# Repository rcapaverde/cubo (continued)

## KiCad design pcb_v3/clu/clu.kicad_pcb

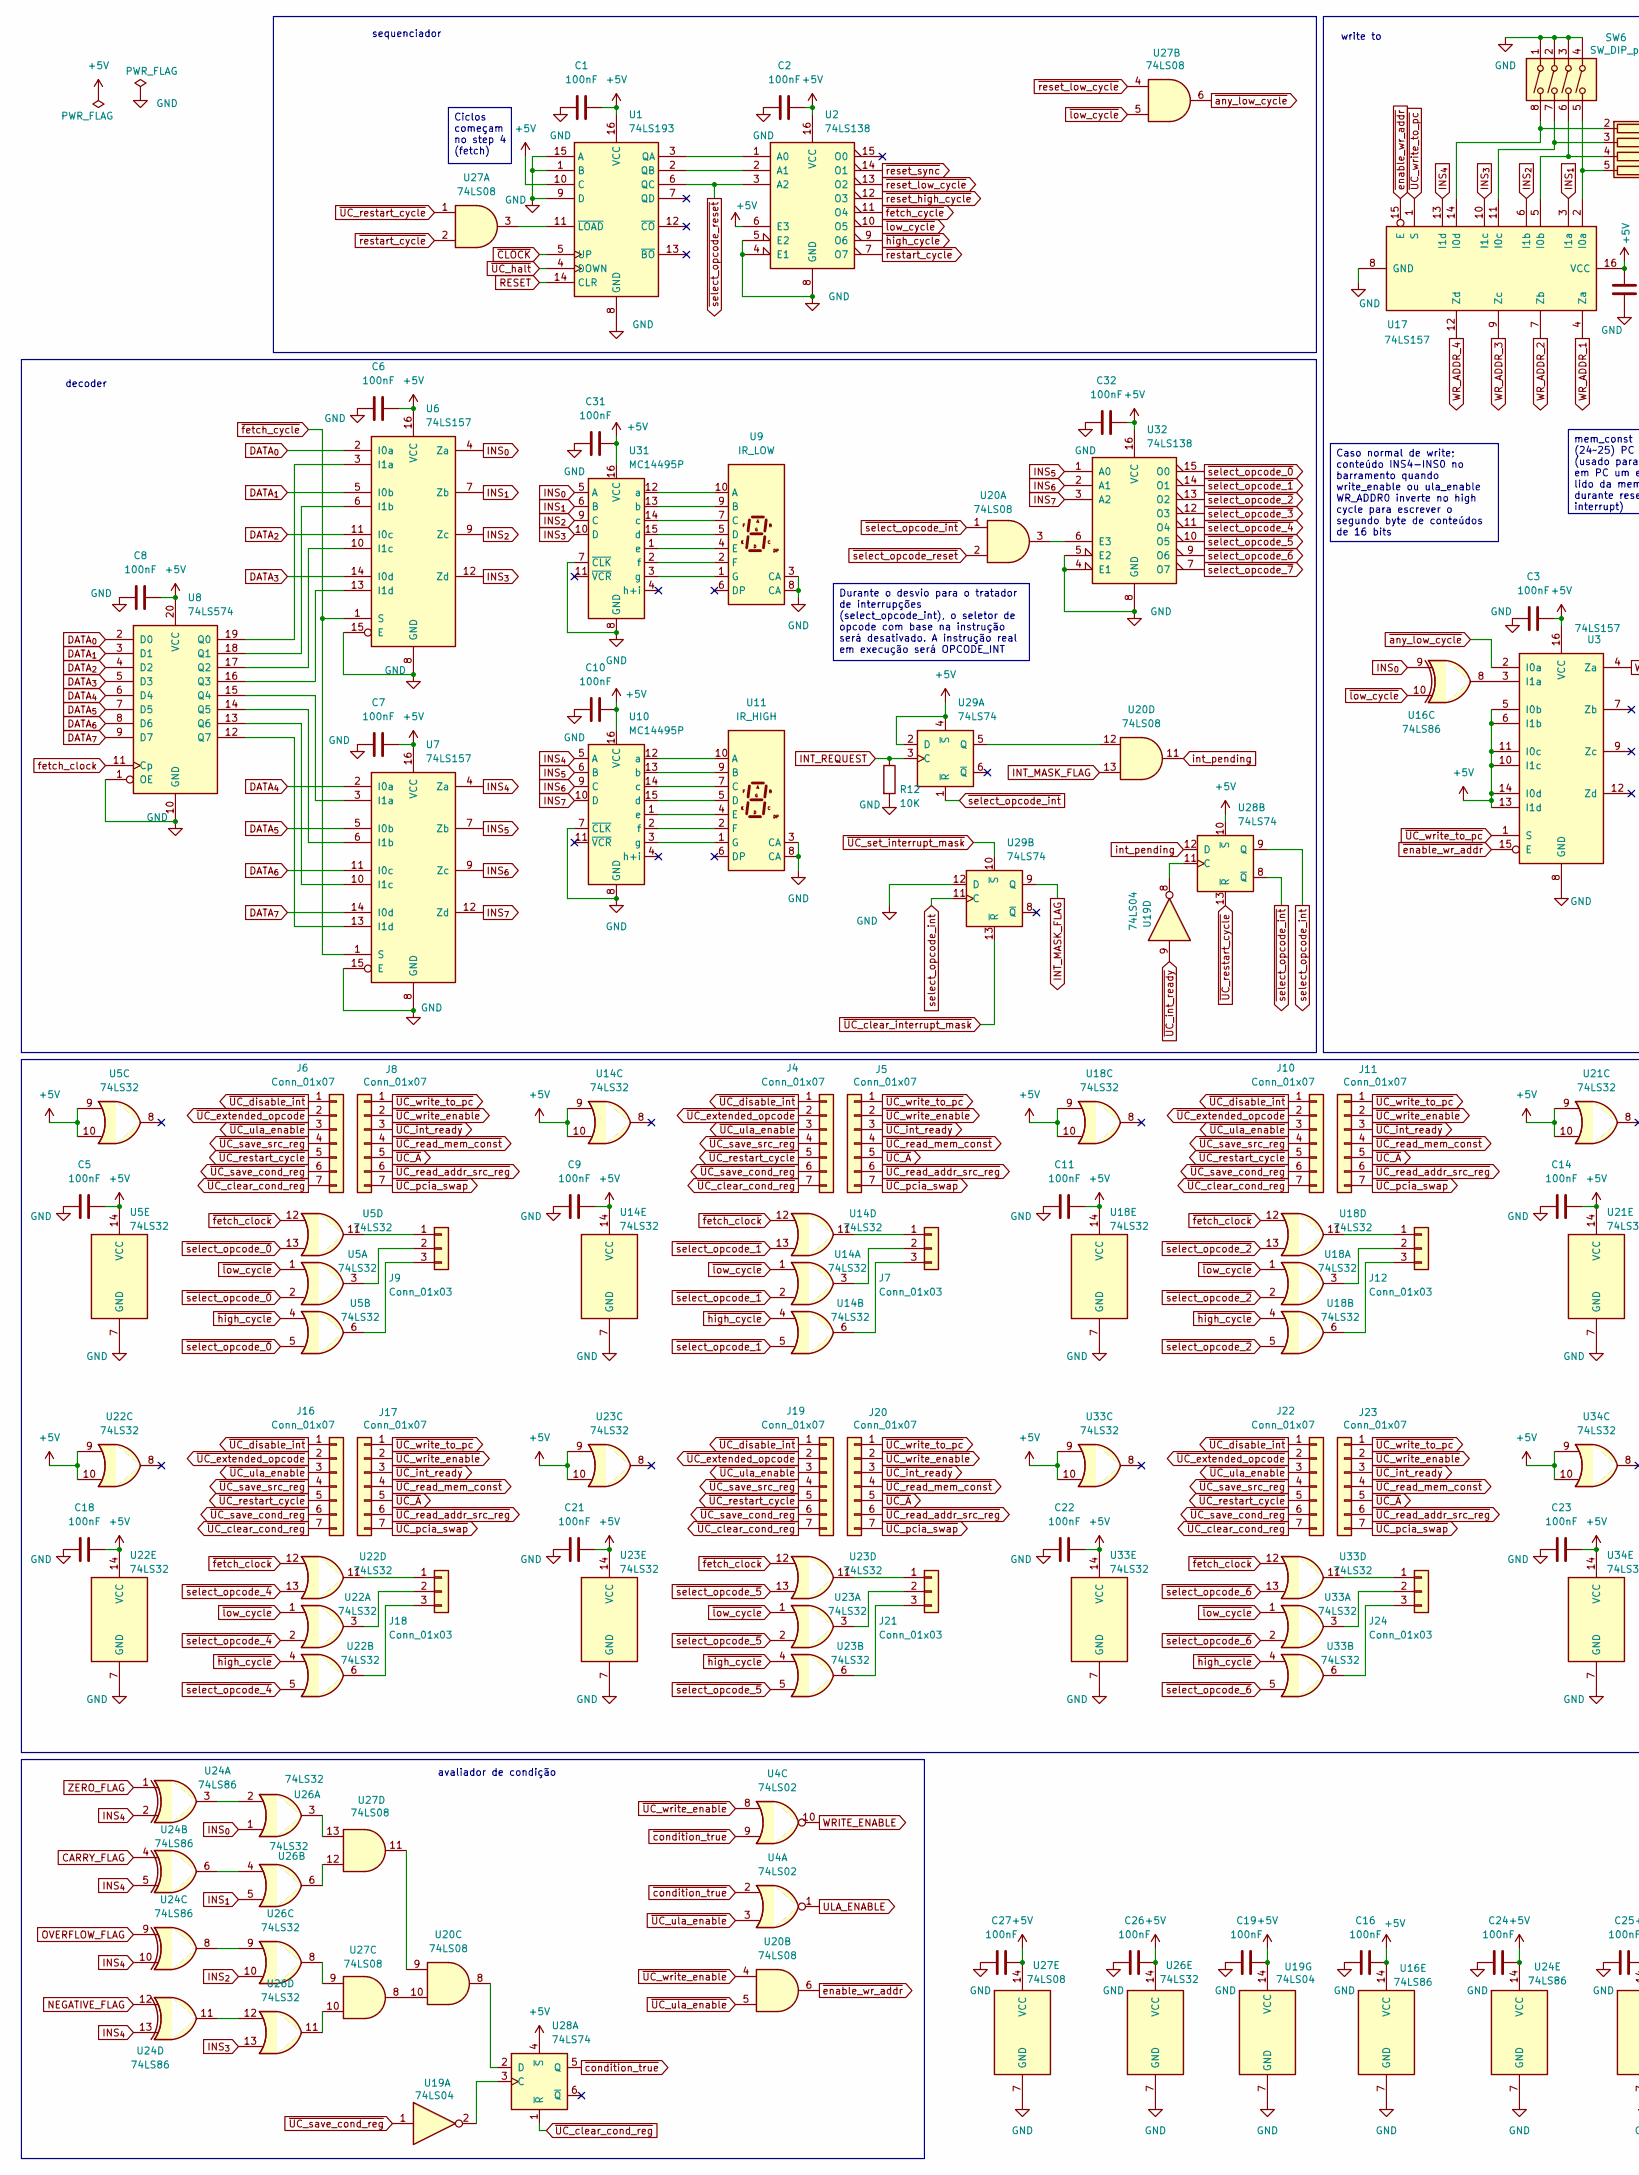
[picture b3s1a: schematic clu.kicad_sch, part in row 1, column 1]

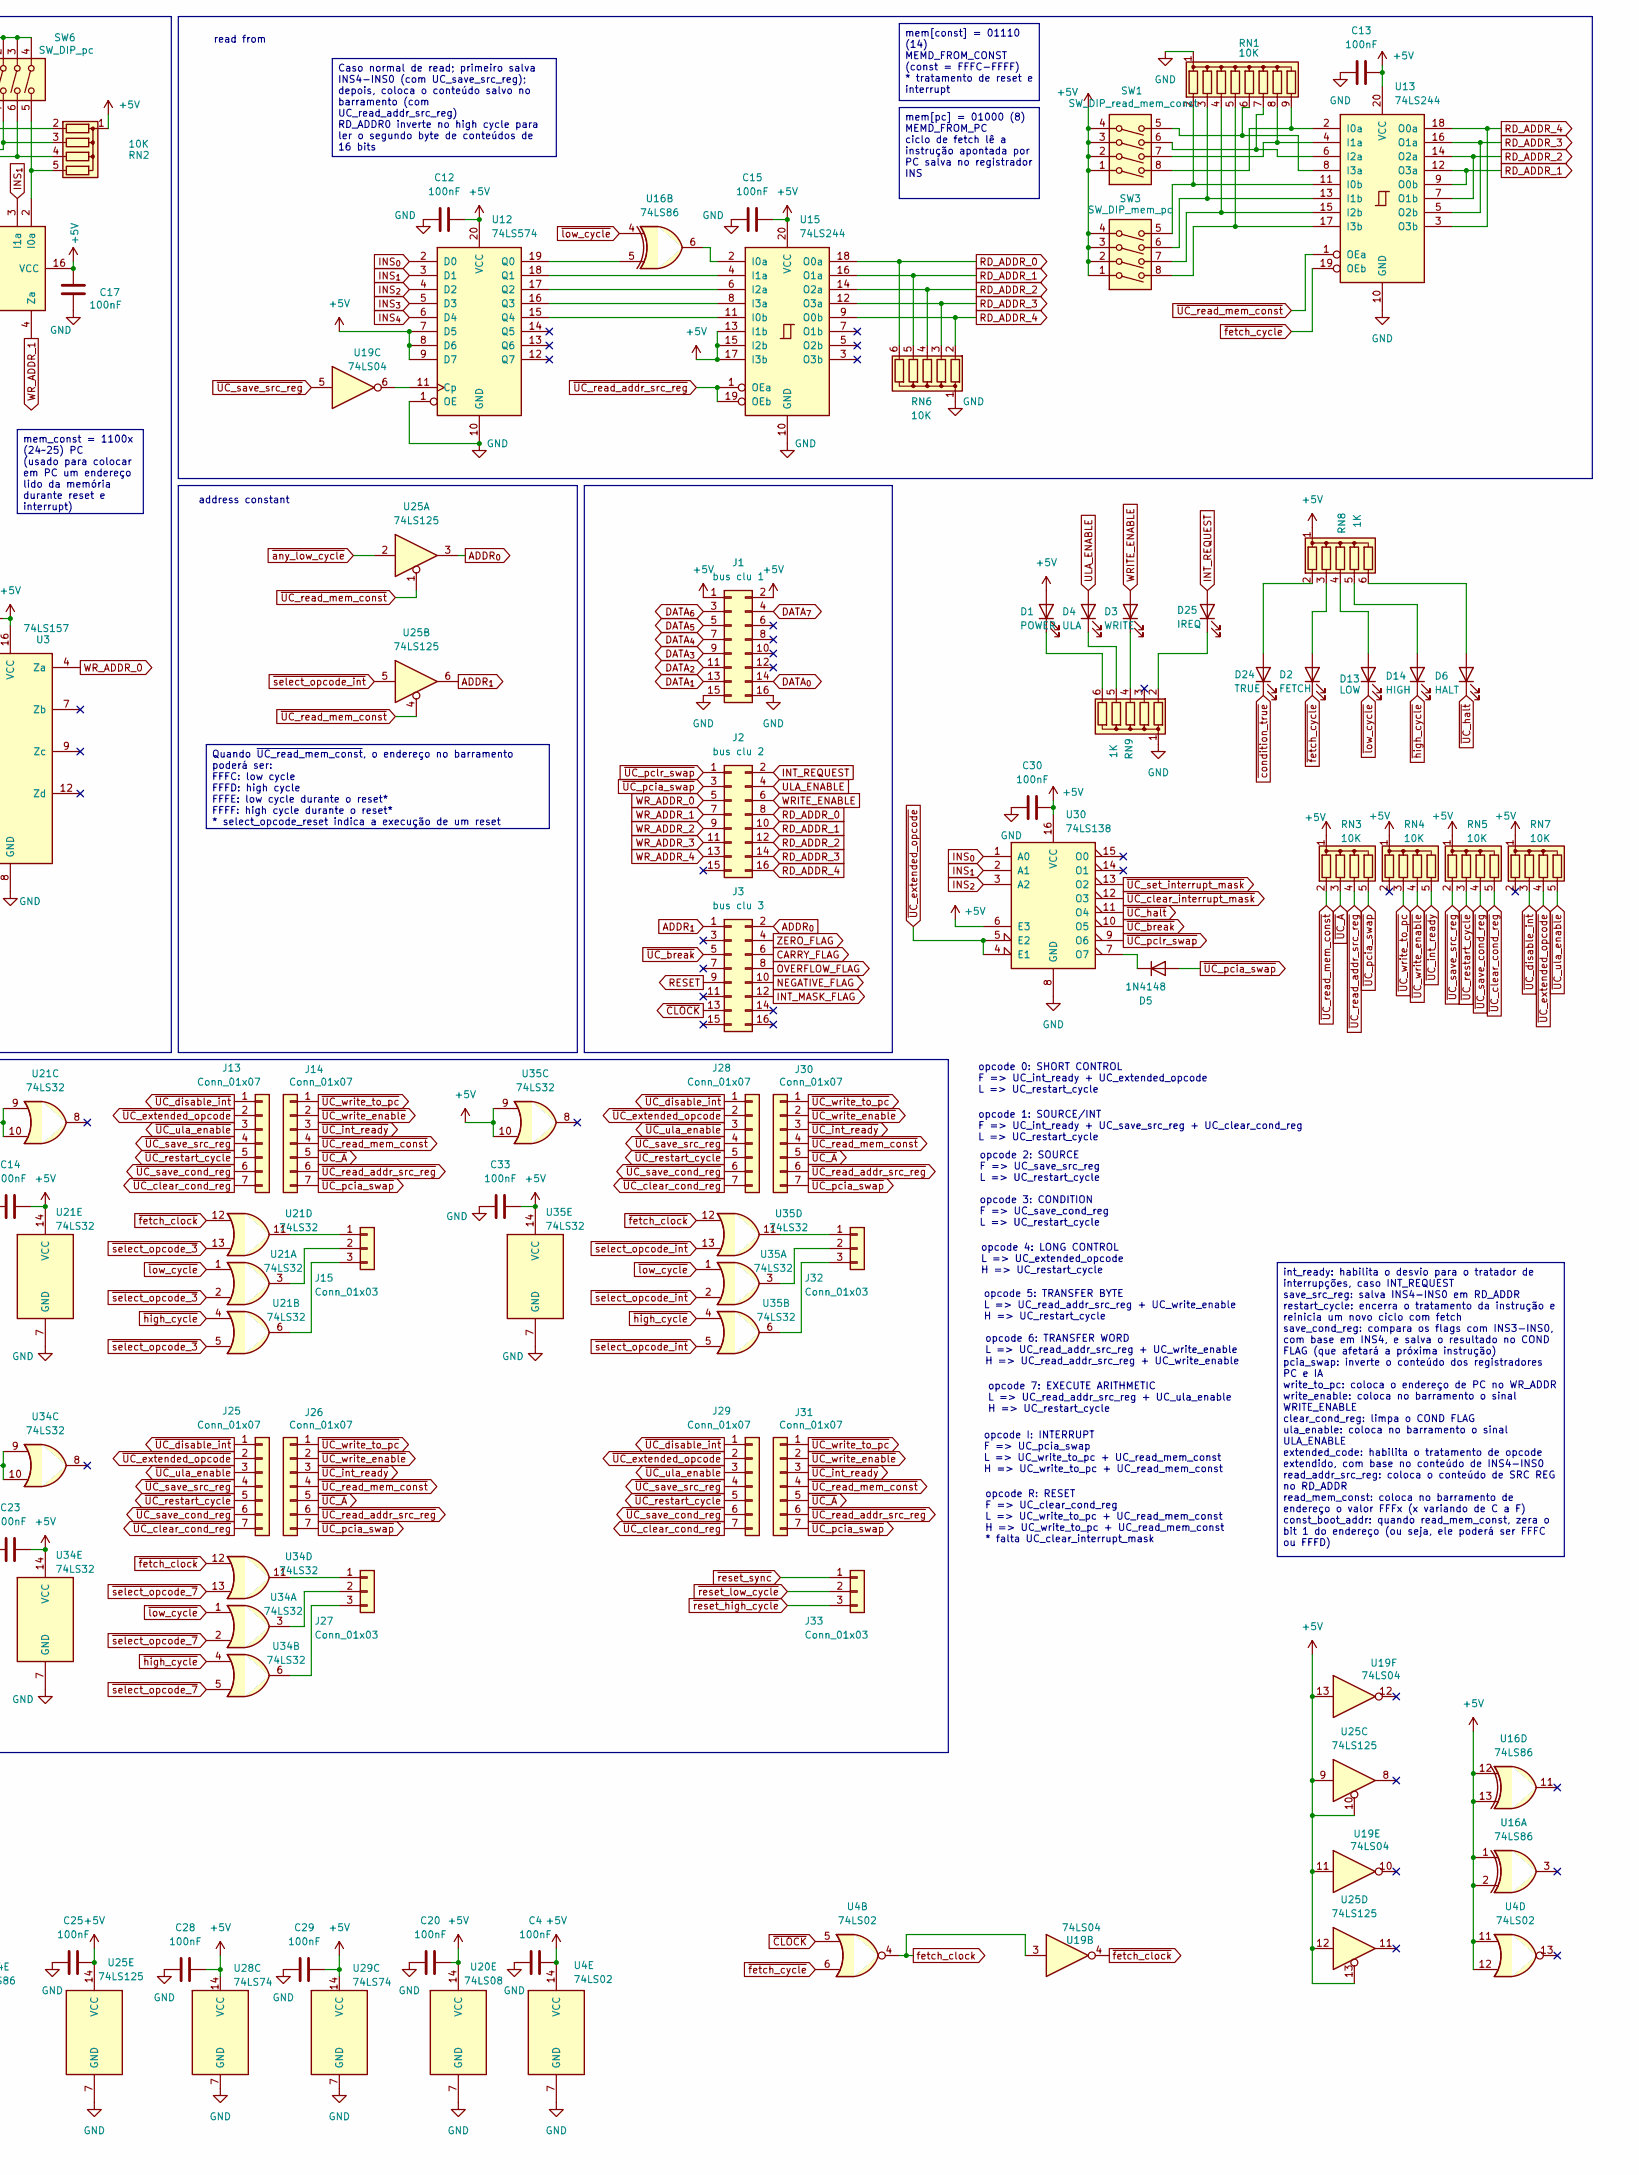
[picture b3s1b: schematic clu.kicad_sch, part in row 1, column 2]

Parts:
C1, C2, C3, C4, C5, C6, C7, C8, C9, C10, C11, C12, C13, C14, C15, C16, C17, C18, C19, C20, C21, C22, C23, C24, C25, C26, C27, C28, C29, C30, C31, C32, C33: 100nF; C_Disc_D5.1mm_W3.2mm_P5.00mm
D1: POWER; LED_D5.0mm
D2: FETCH; LED_D5.0mm
D3: WRITE; LED_D5.0mm
D4: ULA; LED_D5.0mm
D5: 1N4148; D_DO-35_SOD27_P7.62mm_Horizontal
D6: HALT; LED_D5.0mm
D13: LOW; LED_D5.0mm
D14: HIGH; LED_D5.0mm
D24: TRUE; LED_D5.0mm
D25: IREQ; LED_D5.0mm
J1: bus clu 1; conector 02x08
J2: bus clu 2; conector 02x08
J3: bus clu 3; conector 02x08
J4, J5, J6, J8, J10, J11, J13, J14, J16, J17, J19, J20, J22, J23, J25, J26, J28, J29, J30, J31: Conn_01x07; PinHeader_1x07_P2.54mm_Vertical
J7, J9, J12, J15, J18, J21, J24, J27, J32, J33: Conn_01x03; PinHeader_1x03_P2.54mm_Vertical
R12: 10K; R_Axial_DIN0207_L6.3mm_D2.5mm_P7.62mm_Horizontal
RN1: 10K; R_Array_SIP9
RN2, RN3, RN4, RN5, RN7: 10K; R_Array_SIP5
RN6: 10K; R_Array_SIP6
RN8, RN9: 1K; R_Array_SIP6
SW1: SW_DIP_read_mem_const; SW_DIP_SPSTx04_Slide_6.7x11.72mm_W7.62mm_P2.54mm_LowProfile
SW3: SW_DIP_mem_pc; SW_DIP_SPSTx04_Slide_6.7x11.72mm_W7.62mm_P2.54mm_LowProfile
SW6: SW_DIP_pc; SW_DIP_SPSTx04_Slide_6.7x11.72mm_W7.62mm_P2.54mm_LowProfile
U1: 74LS193; DIP-16_W7.62mm
U2, U30, U32: 74LS138; DIP-16_W7.62mm
U3, U6, U7, U17: 74LS157; DIP-16_W7.62mm
U4: 74LS02; DIP-14_W7.62mm
U5, U14, U18, U21, U22, U23, U26, U33, U34, U35: 74LS32; DIP-14_W7.62mm
U8, U12: 74LS574; DIP-20_W7.62mm
U9: IR_LOW; Sx39-1xxxxx
U10, U31: MC14495P; DIP-16_W7.62mm
U11: IR_HIGH; Sx39-1xxxxx
U13, U15: 74LS244; DIP-20_W7.62mm
U16, U24: 74LS86; DIP-14_W7.62mm
U19: 74LS04; DIP-14_W7.62mm
U20, U27: 74LS08; DIP-14_W7.62mm
U25: 74LS125; DIP-14_W7.62mm
U28, U29: 74LS74; DIP-14_W7.62mm

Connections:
+5V: C1.2, C2.2, C3.2, C4.2, C5.2, C6.2, C7.2, C8.2, C9.2, C10.2, C11.2, C12.2, C13.2, C14.2, C15.2, C16.2, C17.2, C18.2, C19.2, C20.2, C21.2, C22.2, C23.2, C24.2, C25.2, C26.2, C27.2, C28.2, C29.2, C30.2, C31.2, C32.2, C33.2, D1.2 (A), J1.1, J1.2, RN2.1 (common), RN3.1 (common), RN4.1 (common), RN5.1 (common), RN7.1 (common), RN8.1 (common), SW1.1, SW1.2, SW1.3, SW1.4, SW3.1, SW3.2, SW3.3, SW3.4, U1.10 (C), U1.16 (VCC), U2.6 (E3), U2.16 (VCC), U3.5 (I0b), U3.6 (I1b), U3.10 (I1c), U3.11 (I0c), U3.13 (I1d), U3.14 (I0d), U3.16 (VCC), U4.11, U4.12, U4.14 (VCC), U5.9, U5.10, U5.14 (VCC), U6.16 (VCC), U7.16 (VCC), U8.20 (VCC), U10.16 (VCC), U12.7 (D5), U12.8 (D6), U12.9 (D7), U12.20 (VCC), U13.20 (VCC), U14.9, U14.10, U14.14 (VCC), U15.13 (I1b), U15.15 (I2b), U15.17 (I3b), U15.20 (VCC), U16.1, U16.2, U16.12, U16.13, U16.14 (VCC), U17.16 (VCC), U18.9, U18.10, U18.14 (VCC), U19.11, U19.13, U19.14 (VCC), U20.14 (VCC), U21.9, U21.10, U21.14 (VCC), U22.9, U22.10, U22.14 (VCC), U23.9, U23.10, U23.14 (VCC), U24.14 (VCC), U25.9, U25.10, U25.12, U25.13, U25.14 (VCC), U26.14 (VCC), U27.14 (VCC), U28.4 (~S), U28.10 (~S), U28.14 (VCC), U29.2 (D), U29.4 (~S), U29.14 (VCC), U30.6 (E3), U30.16 (VCC), U31.16 (VCC), U32.16 (VCC), U33.9, U33.10, U33.14 (VCC), U34.9, U34.10, U34.14 (VCC), U35.9, U35.10, U35.14 (VCC)
ADDR_{0}: J3.2, U25.3
ADDR_{1}: J3.1, U25.6
CARRY_FLAG: J3.6, U24.4
DATA_{0}: J1.14, U6.2 (I0a), U8.2 (D0)
DATA_{1}: J1.13, U6.5 (I0b), U8.3 (D1)
DATA_{2}: J1.11, U6.11 (I0c), U8.4 (D2)
DATA_{3}: J1.9, U6.14 (I0d), U8.5 (D3)
DATA_{4}: J1.7, U7.2 (I0a), U8.6 (D4)
DATA_{5}: J1.5, U7.5 (I0b), U8.7 (D5)
DATA_{6}: J1.3, U7.11 (I0c), U8.8 (D6)
DATA_{7}: J1.4, U7.14 (I0d), U8.9 (D7)
GND: C1.1, C2.1, C3.1, C4.1, C5.1, C6.1, C7.1, C8.1, C9.1, C10.1, C11.1, C12.1, C13.1, C14.1, C15.1, C16.1, C17.1, C18.1, C19.1, C20.1, C21.1, C22.1, C23.1, C24.1, C25.1, C26.1, C27.1, C28.1, C29.1, C30.1, C31.1, C32.1, C33.1, J1.15, J1.16, R12.2, RN1.1 (common), RN6.1 (common), RN9.1 (common), SW6.1, SW6.2, SW6.3, SW6.4, U1.1 (B), U1.8 (GND), U1.9 (D), U1.15 (A), U2.4 (E1), U2.5 (E2), U2.8 (GND), U3.8 (GND), U4.7 (GND), U5.7 (GND), U6.8 (GND), U6.15 (E), U7.8 (GND), U7.15 (E), U8.1 (OE), U8.10 (GND), U9.3 (CA), U9.8 (CA), U10.7 (~CLK), U10.8 (GND), U11.3 (CA), U11.8 (CA), U12.1 (OE), U12.10 (GND), U13.10 (GND), U14.7 (GND), U15.10 (GND), U16.7 (GND), U17.8 (GND), U18.7 (GND), U19.7 (GND), U20.7 (GND), U21.7 (GND), U22.7 (GND), U23.7 (GND), U24.7 (GND), U25.7 (GND), U26.7 (GND), U27.7 (GND), U28.7 (GND), U29.7 (GND), U29.12 (D), U30.8 (GND), U31.7 (~CLK), U31.8 (GND), U32.4 (E1), U32.5 (E2), U32.8 (GND), U33.7 (GND), U34.7 (GND), U35.7 (GND)
INS_{0}: U6.4 (Za), U12.2 (D0), U16.9, U26.1, U30.1 (A0), U31.5 (A)
INS_{1}: U6.7 (Zb), U12.3 (D1), U17.3 (I1a), U26.5, U30.2 (A1), U31.6 (B)
INS_{2}: U6.9 (Zc), U12.4 (D2), U17.6 (I1b), U26.10, U30.3 (A2), U31.9 (C)
INS_{3}: U6.12 (Zd), U12.5 (D3), U17.10 (I1c), U26.13, U31.10 (D)
INS_{4}: U7.4 (Za), U10.5 (A), U12.6 (D4), U17.13 (I1d), U24.2, U24.5, U24.10, U24.13
INS_{5}: U7.7 (Zb), U10.6 (B), U32.1 (A0)
INS_{6}: U7.9 (Zc), U10.9 (C), U32.2 (A1)
INS_{7}: U7.12 (Zd), U10.10 (D), U32.3 (A2)
INT_MASK_FLAG: J3.12, U20.13, U29.9 (Q)
INT_REQUEST: D25.2 (A), J2.2, R12.1, U29.3 (C)
NEGATIVE_FLAG: J3.10, U24.12
unnamed: D1.1 (K), RN9.6 (R5)
unnamed: D2.2 (A), RN8.3 (R2)
unnamed: D3.1 (K), RN9.4 (R3)
unnamed: D4.1 (K), RN9.5 (R4)
unnamed: D5.1 (K), U30.7 (O7)
unnamed: D6.2 (A), RN8.6 (R5)
unnamed: D13.2 (A), RN8.4 (R3)
unnamed: D14.2 (A), RN8.5 (R4)
unnamed: D24.2 (A), RN8.2 (R1)
unnamed: D25.1 (K), RN9.2 (R1)
unnamed: J7.1, U14.11
unnamed: J7.2, U14.3
unnamed: J7.3, U14.6
unnamed: J9.1, U5.11
unnamed: J9.2, U5.3
unnamed: J9.3, U5.6
unnamed: J12.1, U18.11
unnamed: J12.2, U18.3
unnamed: J12.3, U18.6
unnamed: J15.1, U21.11
unnamed: J15.2, U21.3
unnamed: J15.3, U21.6
unnamed: J18.1, U22.11
unnamed: J18.2, U22.3
unnamed: J18.3, U22.6
unnamed: J21.1, U23.11
unnamed: J21.2, U23.3
unnamed: J21.3, U23.6
unnamed: J24.1, U33.11
unnamed: J24.2, U33.3
unnamed: J24.3, U33.6
unnamed: J27.1, U34.11
unnamed: J27.2, U34.3
unnamed: J27.3, U34.6
unnamed: J32.1, U35.11
unnamed: J32.2, U35.3
unnamed: J32.3, U35.6
unnamed: RN1.2 (R1), SW3.5, U13.11 (I0b)
unnamed: RN1.3 (R2), SW3.6, U13.13 (I1b)
unnamed: RN1.4 (R3), SW3.7, U13.15 (I2b)
unnamed: RN1.5 (R4), SW3.8, U13.17 (I3b)
unnamed: RN1.6 (R5), SW1.5, U13.8 (I3a)
unnamed: RN1.7 (R6), SW1.6, U13.6 (I2a)
unnamed: RN1.8 (R7), SW1.7, U13.4 (I1a)
unnamed: RN1.9 (R8), SW1.8, U13.2 (I0a)
unnamed: RN2.2 (R1), SW6.8, U17.14 (I0d)
unnamed: RN2.3 (R2), SW6.7, U17.11 (I0c)
unnamed: RN2.4 (R3), SW6.6, U17.5 (I0b)
unnamed: RN2.5 (R4), SW6.5, U17.2 (I0a)
unnamed: U1.3 (QA), U2.1 (A0)
unnamed: U1.2 (QB), U2.2 (A1)
unnamed: U1.11 (~LOAD), U27.3
unnamed: U3.3 (I1a), U16.8
unnamed: U6.3 (I1a), U8.19 (Q0)
unnamed: U6.6 (I1b), U8.18 (Q1)
unnamed: U6.10 (I1c), U8.17 (Q2)
unnamed: U6.13 (I1d), U8.16 (Q3)
unnamed: U7.3 (I1a), U8.15 (Q4)
unnamed: U7.6 (I1b), U8.14 (Q5)
unnamed: U7.10 (I1c), U8.13 (Q6)
unnamed: U7.13 (I1d), U8.12 (Q7)
unnamed: U10.12 (a), U11.10 (A)
unnamed: U10.13 (b), U11.9 (B)
unnamed: U10.14 (c), U11.7 (C)
unnamed: U10.15 (d), U11.5 (D)
unnamed: U10.1 (e), U11.4 (E)
unnamed: U10.2 (f), U11.2 (F)
unnamed: U10.3 (g), U11.1 (G)
unnamed: U12.11 (Cp), U19.6
unnamed: U12.19 (Q0), U16.5
unnamed: U12.18 (Q1), U15.4 (I1a)
unnamed: U12.17 (Q2), U15.6 (I2a)
unnamed: U12.16 (Q3), U15.8 (I3a)
unnamed: U12.15 (Q4), U15.11 (I0b)
unnamed: U15.2 (I0a), U16.6
unnamed: U20.9, U27.11
unnamed: U20.10, U27.8
unnamed: U24.3, U26.2
unnamed: U24.6, U26.4
unnamed: U24.8, U26.9
unnamed: U24.11, U26.12
unnamed: U26.3, U27.13
unnamed: U26.6, U27.12
unnamed: U26.8, U27.9
unnamed: U26.11, U27.10
unnamed: U19.2, U28.3 (C)
unnamed: U20.8, U28.2 (D)
unnamed: U19.8, U28.11 (C)
unnamed: U20.12, U29.5 (Q)
unnamed: U9.10 (A), U31.12 (a)
unnamed: U9.9 (B), U31.13 (b)
unnamed: U9.7 (C), U31.14 (c)
unnamed: U9.5 (D), U31.15 (d)
unnamed: U9.4 (E), U31.1 (e)
unnamed: U9.2 (F), U31.2 (f)
unnamed: U9.1 (G), U31.3 (g)
unnamed: U20.3, U32.6 (E3)
OVERFLOW_FLAG: J3.8, U24.9
RD_ADDR_0: J2.8, RN6.6 (R5), U15.18 (O0a)
RD_ADDR_1: J2.10, RN6.5 (R4), U13.9 (O0b), U13.12 (O3a), U15.16 (O1a)
RD_ADDR_2: J2.12, RN6.4 (R3), U13.7 (O1b), U13.14 (O2a), U15.14 (O2a)
RD_ADDR_3: J2.14, RN6.3 (R2), U13.5 (O2b), U13.16 (O1a), U15.12 (O3a)
RD_ADDR_4: J2.16, RN6.2 (R1), U13.3 (O3b), U13.18 (O0a), U15.9 (O0b)
RESET: J3.9, U1.14 (CLR)
ULA_ENABLE: D4.2 (A), J2.4, U4.1
WRITE_ENABLE: D3.2 (A), J2.6, U4.10
WR_ADDR_0: J2.5, U3.4 (Za)
WR_ADDR_1: J2.7, U17.4 (Za)
WR_ADDR_2: J2.9, U17.7 (Zb)
WR_ADDR_3: J2.11, U17.9 (Zc)
WR_ADDR_4: J2.13, U17.12 (Zd)
ZERO_FLAG: J3.4, U24.1
fetch_clock: U4.4, U8.11 (Cp), U19.3
int_pending: U20.11, U28.12 (D)
select_opcode_int: U28.9 (Q), U29.11 (C)
~CLOCK: J3.13, U1.5 (UP), U4.5
~UC_A: J5.5, J8.5, J11.5, J14.5, J17.5, J20.5, J23.5, J26.5, J30.5, J31.5, RN3.3 (R2)
~UC_break: J3.5, U30.10 (O5)
~UC_clear_cond_reg: J4.7, J6.7, J10.7, J13.7, J16.7, J19.7, J22.7, J25.7, J28.7, J29.7, RN5.5 (R4), U28.1 (~R)
~UC_clear_interrupt_mask: U29.13 (~R), U30.12 (O3)
~UC_disable_int: J4.1, J6.1, J10.1, J13.1, J16.1, J19.1, J22.1, J25.1, J28.1, J29.1, RN7.3 (R2)
~UC_extended_opcode: J4.2, J6.2, J10.2, J13.2, J16.2, J19.2, J22.2, J25.2, J28.2, J29.2, RN7.4 (R3), U30.4 (E1), U30.5 (E2)
~UC_halt: D6.1 (K), U1.4 (DOWN), U30.11 (O4)
~UC_int_ready: J5.3, J8.3, J11.3, J14.3, J17.3, J20.3, J23.3, J26.3, J30.3, J31.3, RN4.5 (R4), U19.9
~UC_pcia_swap: D5.2 (A), J2.3, J5.7, J8.7, J11.7, J14.7, J17.7, J20.7, J23.7, J26.7, J30.7, J31.7, RN3.5 (R4)
~UC_pclr_swap: J2.1, U30.9 (O6)
~UC_read_addr_src_reg: J5.6, J8.6, J11.6, J14.6, J17.6, J20.6, J23.6, J26.6, J30.6, J31.6, RN3.4 (R3), U15.1 (OEa), U15.19 (OEb)
~UC_read_mem_const: J5.4, J8.4, J11.4, J14.4, J17.4, J20.4, J23.4, J26.4, J30.4, J31.4, RN3.2 (R1), U13.1 (OEa), U25.1, U25.4
~UC_restart_cycle: J4.5, J6.5, J10.5, J13.5, J16.5, J19.5, J22.5, J25.5, J28.5, J29.5, RN5.3 (R2), U27.1, U28.13 (~R)
~UC_save_cond_reg: J4.6, J6.6, J10.6, J13.6, J16.6, J19.6, J22.6, J25.6, J28.6, J29.6, RN5.4 (R3), U19.1
~UC_save_src_reg: J4.4, J6.4, J10.4, J13.4, J16.4, J19.4, J22.4, J25.4, J28.4, J29.4, RN5.2 (R1), U19.5
~UC_set_interrupt_mask: U29.10 (~S), U30.13 (O2)
~UC_ula_enable: J4.3, J6.3, J10.3, J13.3, J16.3, J19.3, J22.3, J25.3, J28.3, J29.3, RN7.5 (R4), U4.3, U20.5
~UC_write_enable: J5.2, J8.2, J11.2, J14.2, J17.2, J20.2, J23.2, J26.2, J30.2, J31.2, RN4.4 (R3), U4.8, U20.4
~UC_write_to_pc: J5.1, J8.1, J11.1, J14.1, J17.1, J20.1, J23.1, J26.1, J30.1, J31.1, RN4.3 (R2), U3.1 (S), U17.1 (S)
~any_low_cycle: U3.2 (I0a), U25.2, U27.6
~condition_true: D24.1 (K), U4.2, U4.9, U28.5 (Q)
~enable_wr_addr: U3.15 (E), U17.15 (E), U20.6
~fetch_clock: U5.12, U14.12, U18.12, U19.4, U21.12, U22.12, U23.12, U33.12, U34.12, U35.12
~fetch_cycle: D2.1 (K), U2.11 (O4), U4.6, U6.1 (S), U7.1 (S), U13.19 (OEb)
~high_cycle: D14.1 (K), U2.9 (O6), U5.4, U14.4, U18.4, U21.4, U22.4, U23.4, U33.4, U34.4, U35.4
~low_cycle: D13.1 (K), U2.10 (O5), U5.1, U14.1, U16.4, U16.10, U18.1, U21.1, U22.1, U23.1, U27.5, U33.1, U34.1, U35.1
~reset_high_cycle: J33.3, U2.12 (O3)
~reset_low_cycle: J33.2, U2.13 (O2), U27.4
~reset_sync: J33.1, U2.14 (O1)
~restart_cycle: U2.7 (O7), U27.2
~select_opcode_0: U5.2, U5.5, U5.13, U32.15 (O0)
~select_opcode_1: U14.2, U14.5, U14.13, U32.14 (O1)
~select_opcode_2: U18.2, U18.5, U18.13, U32.13 (O2)
~select_opcode_3: U21.2, U21.5, U21.13, U32.12 (O3)
~select_opcode_4: U22.2, U22.5, U22.13, U32.11 (O4)
~select_opcode_5: U23.2, U23.5, U23.13, U32.10 (O5)
~select_opcode_6: U32.9 (O6), U33.2, U33.5, U33.13
~select_opcode_7: U32.7 (O7), U34.2, U34.5, U34.13
~select_opcode_int: U20.1, U25.5, U28.8 (~Q), U29.1 (~R), U35.2, U35.5, U35.13
~select_opcode_reset: U1.6 (QC), U2.3 (A2), U20.2

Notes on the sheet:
opcode 1: SOURCE/INT F => UC_int_ready + UC_save_src_reg + UC_clear_cond_reg L => UC_restart_cycle
opcode 2: SOURCE F => UC_save_src_reg L => UC_restart_cycle
sequenciador
write to
opcode 7: EXECUTE ARITHMETIC L => UC_read_addr_src_reg + UC_ula_enable H => UC_restart_cycle
avaliador de condição
decoder
read from
opcode 6: TRANSFER WORD L => UC_read_addr_src_reg + UC_write_enable H => UC_read_addr_src_reg + UC_write_enable
address constant
opcode R: RESET F => UC_clear_cond_reg L => UC_write_to_pc + UC_read_mem_const H => UC_write_to_pc + UC_read_mem_const * falta UC_clear_interrupt_mask
opcode 4: LONG CONTROL L => UC_extended_opcode H => UC_restart_cycle
opcode I: INTERRUPT F => UC_pcia_swap L => UC_write_to_pc + UC_read_mem_const H => UC_write_to_pc + UC_read_mem_const
opcode 3: CONDITION F => UC_save_cond_reg L => UC_restart_cycle
opcode 0: SHORT CONTROL F => UC_int_ready + UC_extended_opcode L => UC_restart_cycle
opcode 5: TRANSFER BYTE L => UC_read_addr_src_reg + UC_write_enable H => UC_restart_cycle
Caso normal de read; primeiro salva INS4-INS0 (com UC_save_src_reg); depois, coloca o conteúdo salvo no barramento (com UC_read_addr_src_reg) RD_ADDR0 inverte no high cycle para ler o segundo byte de conteúdos de 16 bits
mem_const = 1100x (24~25) PC (usado para colocar em PC um endereço lido da memória durante reset e interrupt)
Caso normal de write; conteúdo INS4-INS0 no barramento quando write_enable ou ula_enable WR_ADDR0 inverte no high cycle para escrever o segundo byte de conteúdos de 16 bits
Quando ~{UC_read_mem_const}, o endereço no barramento poderá ser: FFFC: low cycle FFFD: high cycle FFFE: low cycle durante o reset* FFFF: high cycle durante o reset* * select_opcode_reset indica a execução de um reset
Durante o desvio para o tratador de interrupções (select_opcode_int), o seletor de opcode com base na instrução será desativado. A instrução real em execução será OPCODE_INT
int_ready: habilita o desvio para o tratador de interrupções, caso INT_REQUEST save_src_reg: salva INS4-INS0 em RD_ADDR restart_cycle: encerra o tratamento da instrução e reinicia um novo ciclo com fetch save_cond_reg: compara os flags com INS3-INS0, com base em INS4, e salva o resultado no COND FL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
mem[pc] = 01000 (8) MEMD_FROM_PC ciclo de fetch lê a instrução apontada por PC salva no registrador INS
Ciclos começam no step 4 (fetch)
mem[const] = 01110 (14) MEMD_FROM_CONST (const = FFFC-FFFF) * tratamento de reset e interrupt

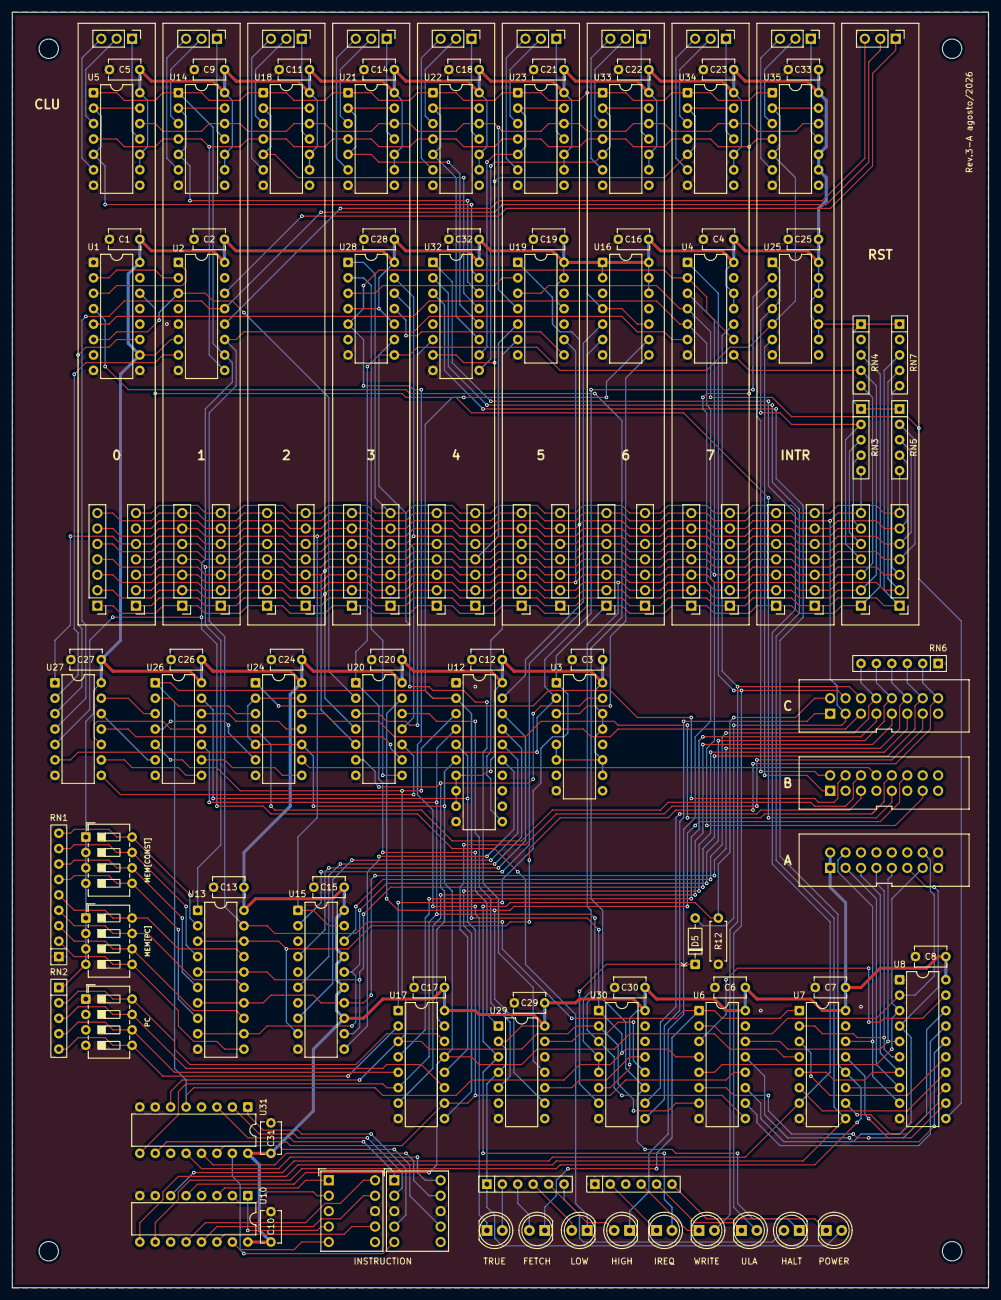
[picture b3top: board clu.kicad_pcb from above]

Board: 2 copper layers, 160.7 x 210.0 mm, 124 parts (0 on the bottom side), 180 nets.

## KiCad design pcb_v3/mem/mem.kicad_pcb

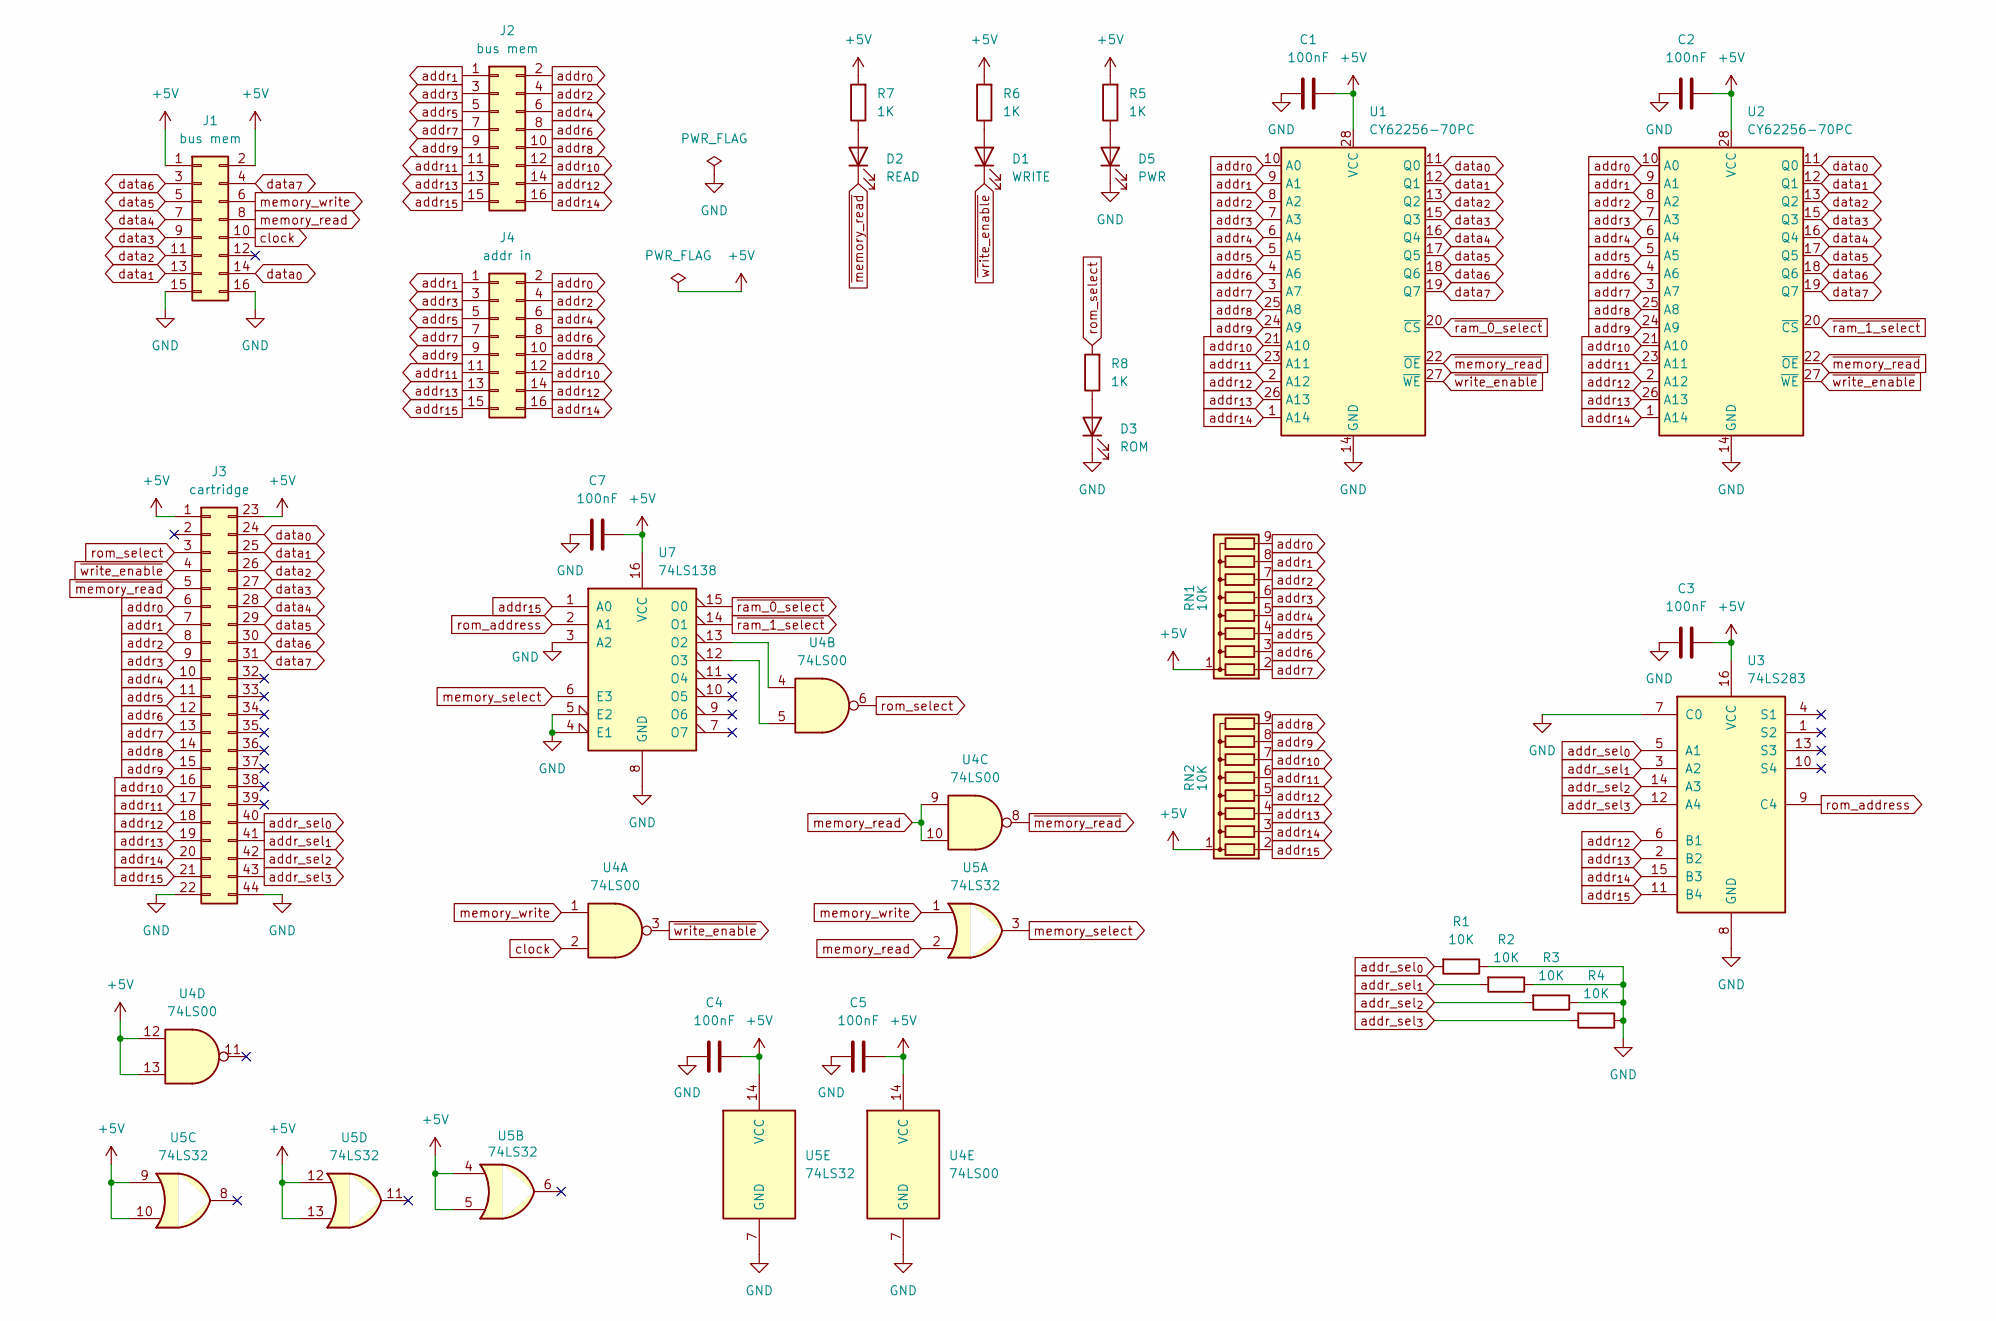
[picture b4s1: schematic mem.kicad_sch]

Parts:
C1, C2, C3, C4, C5, C7: 100nF; C_Disc_D5.1mm_W3.2mm_P5.00mm
D1: WRITE; LED_D5.0mm
D2: READ; LED_D5.0mm
D3: ROM; LED_D5.0mm
D5: PWR; LED_D5.0mm
J1, J2: bus mem; conector 02x08
J3: cartridge; male-edge-connector-44
J4: addr in; conector 02x08
R1, R2, R3, R4: 10K; R_Axial_DIN0207_L6.3mm_D2.5mm_P7.62mm_Horizontal
R5, R6, R7, R8: 1K; R_Axial_DIN0207_L6.3mm_D2.5mm_P7.62mm_Horizontal
RN1, RN2: 10K; R_Array_SIP9
U1, U2: CY62256-70PC; DIP-28_W15.24mm
U3: 74LS283; DIP-16_W7.62mm
U4: 74LS00; DIP-14_W7.62mm
U5: 74LS32; DIP-14_W7.62mm
U7: 74LS138; DIP-16_W7.62mm

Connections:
+5V: C1.2, C2.2, C3.2, C4.2, C5.2, C7.2, J1.1, J1.2, J3.1, J3.23, R5.2, R6.2, R7.2, RN1.1 (common), RN2.1 (common), U1.28 (VCC), U2.28 (VCC), U3.16 (VCC), U4.12, U4.13, U4.14 (VCC), U5.4, U5.5, U5.9, U5.10, U5.12, U5.13, U5.14 (VCC), U7.16 (VCC)
GND: C1.1, C2.1, C3.1, C4.1, C5.1, C7.1, D3.1 (K), D5.1 (K), J1.15, J1.16, J3.22, J3.44, R1.1, R2.1, R3.1, R4.1, U1.14 (GND), U2.14 (GND), U3.7 (C0), U3.8 (GND), U4.7 (GND), U5.7 (GND), U7.3 (A2), U7.4 (E1), U7.5 (E2), U7.8 (GND)
unnamed: D1.2 (A), R6.1
unnamed: D2.2 (A), R7.1
unnamed: D3.2 (A), R8.1
unnamed: D5.2 (A), R5.1
unnamed: U4.4, U7.13 (O2)
unnamed: U4.5, U7.12 (O3)
addr_sel_{0}: J3.40, R1.2, U3.5 (A1)
addr_sel_{1}: J3.41, R2.2, U3.3 (A2)
addr_sel_{2}: J3.42, R3.2, U3.14 (A3)
addr_sel_{3}: J3.43, R4.2, U3.12 (A4)
addr_{0}: J2.2, J3.6, J4.2, RN1.9 (R8), U1.10 (A0), U2.10 (A0)
addr_{1}: J2.1, J3.7, J4.1, RN1.8 (R7), U1.9 (A1), U2.9 (A1)
addr_{2}: J2.4, J3.8, J4.4, RN1.7 (R6), U1.8 (A2), U2.8 (A2)
addr_{3}: J2.3, J3.9, J4.3, RN1.6 (R5), U1.7 (A3), U2.7 (A3)
addr_{4}: J2.6, J3.10, J4.6, RN1.5 (R4), U1.6 (A4), U2.6 (A4)
addr_{5}: J2.5, J3.11, J4.5, RN1.4 (R3), U1.5 (A5), U2.5 (A5)
addr_{6}: J2.8, J3.12, J4.8, RN1.3 (R2), U1.4 (A6), U2.4 (A6)
addr_{7}: J2.7, J3.13, J4.7, RN1.2 (R1), U1.3 (A7), U2.3 (A7)
addr_{8}: J2.10, J3.14, J4.10, RN2.9 (R8), U1.25 (A8), U2.25 (A8)
addr_{9}: J2.9, J3.15, J4.9, RN2.8 (R7), U1.24 (A9), U2.24 (A9)
addr_{10}: J2.12, J3.16, J4.12, RN2.7 (R6), U1.21 (A10), U2.21 (A10)
addr_{11}: J2.11, J3.17, J4.11, RN2.6 (R5), U1.23 (A11), U2.23 (A11)
addr_{12}: J2.14, J3.18, J4.14, RN2.5 (R4), U1.2 (A12), U2.2 (A12), U3.6 (B1)
addr_{13}: J2.13, J3.19, J4.13, RN2.4 (R3), U1.26 (A13), U2.26 (A13), U3.2 (B2)
addr_{14}: J2.16, J3.20, J4.16, RN2.3 (R2), U1.1 (A14), U2.1 (A14), U3.15 (B3)
addr_{15}: J2.15, J3.21, J4.15, RN2.2 (R1), U3.11 (B4), U7.1 (A0)
clock: J1.10, U4.2
data_{0}: J1.14, J3.24, U1.11 (Q0), U2.11 (Q0)
data_{1}: J1.13, J3.25, U1.12 (Q1), U2.12 (Q1)
data_{2}: J1.11, J3.26, U1.13 (Q2), U2.13 (Q2)
data_{3}: J1.9, J3.27, U1.15 (Q3), U2.15 (Q3)
data_{4}: J1.7, J3.28, U1.16 (Q4), U2.16 (Q4)
data_{5}: J1.5, J3.29, U1.17 (Q5), U2.17 (Q5)
data_{6}: J1.3, J3.30, U1.18 (Q6), U2.18 (Q6)
data_{7}: J1.4, J3.31, U1.19 (Q7), U2.19 (Q7)
memory_read: J1.8, U4.9, U4.10, U5.2
memory_select: U5.3, U7.6 (E3)
memory_write: J1.6, U4.1, U5.1
rom_address: U3.9 (C4), U7.2 (A1)
rom_select: J3.3, R8.2, U4.6
~memory_read: D2.1 (K), J3.5, U1.22 (~OE), U2.22 (~OE), U4.8
~ram_0_select: U1.20 (~CS), U7.15 (O0)
~ram_1_select: U2.20 (~CS), U7.14 (O1)
~write_enable: D1.1 (K), J3.4, U1.27 (~WE), U2.27 (~WE), U4.3

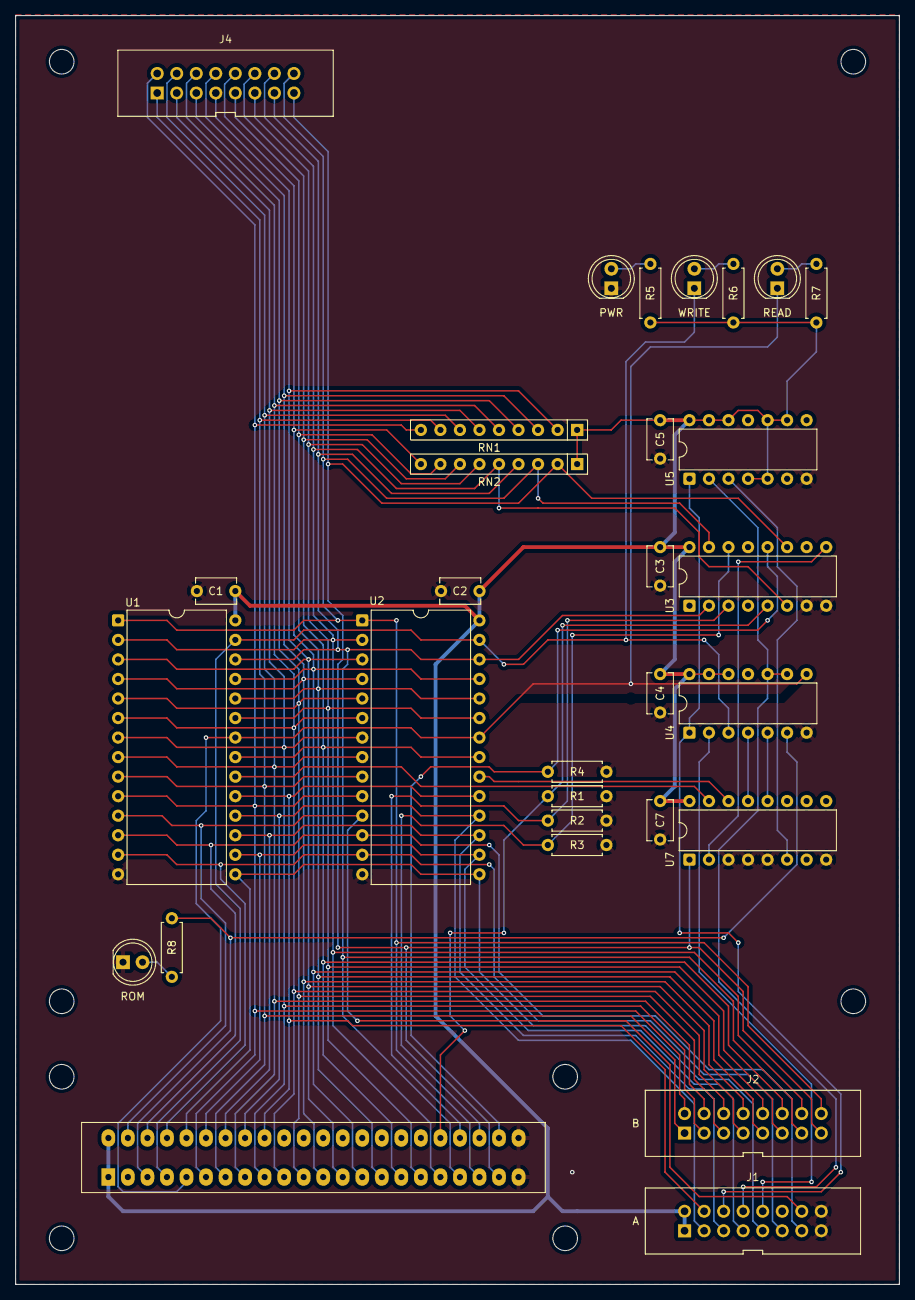
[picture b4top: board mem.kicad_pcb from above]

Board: 2 copper layers, 114.9 x 165.0 mm, 30 parts (0 on the bottom side), 46 nets.
